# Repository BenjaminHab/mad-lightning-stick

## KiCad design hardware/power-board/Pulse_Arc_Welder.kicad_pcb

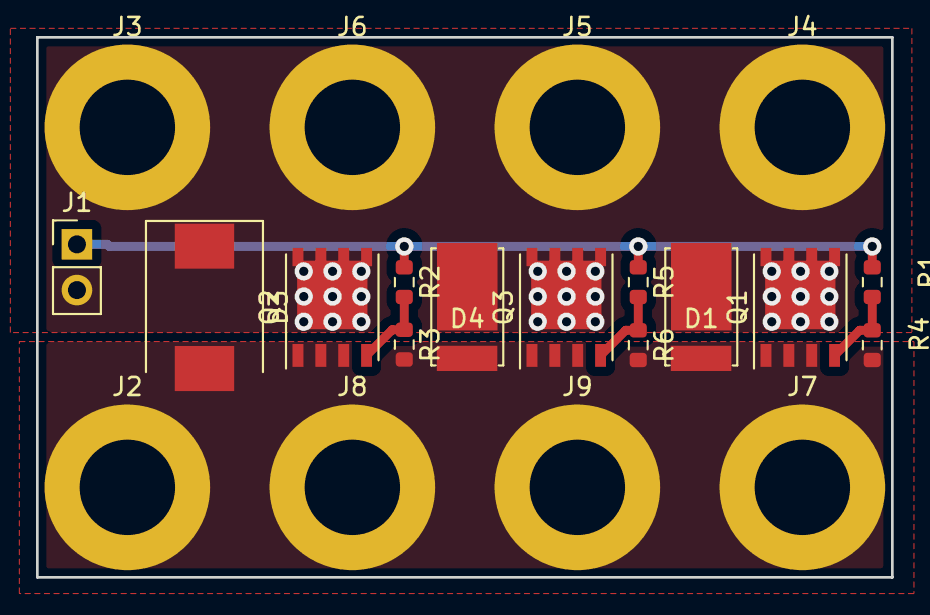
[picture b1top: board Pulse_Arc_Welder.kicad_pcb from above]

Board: 2 copper layers, 47.5 x 30.0 mm, 21 parts (0 on the bottom side), 6 nets.

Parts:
D1, D4: SBR10U45SP5; powerdi5
D3: 24V; D_SMC
J1: to logic board; PinHeader_1x02_P2.54mm_Vertical
J2, J7, J8, J9: BAT-; MountingHole_5.3mm_M5_DIN965_Pad
J3, J4, J5, J6: Electrode; MountingHole_5.3mm_M5_DIN965_Pad
Q1, Q2, Q3: SIR500DP-T1-RE3; PowerPAK_SO-8_Single
R1, R2, R5: 10R; R_0603_1608Metric
R3, R4, R6: 10k; R_0603_1608Metric

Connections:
Electrode: D1.1 (K), D3.1 (K), D4.1 (K), J1.2, J3.1, J4.1, J5.1, J6.1, Q1.5 (D), Q2.5 (D), Q3.5 (D)
GND: D1.2 (A), D3.2 (A), D4.2 (A), J2.1, J7.1, J8.1, J9.1, Q1.1 (S), Q1.2 (S), Q1.3 (S), Q2.1 (S), Q2.2 (S), Q2.3 (S), Q3.1 (S), Q3.2 (S), Q3.3 (S), R3.2, R4.2, R6.2
unnamed: Q2.4 (G), R2.2, R3.1
unnamed: Q3.4 (G), R5.2, R6.1
unnamed: Q1.4 (G), R1.2, R4.1
SIG: J1.1, R1.1, R2.1, R5.1

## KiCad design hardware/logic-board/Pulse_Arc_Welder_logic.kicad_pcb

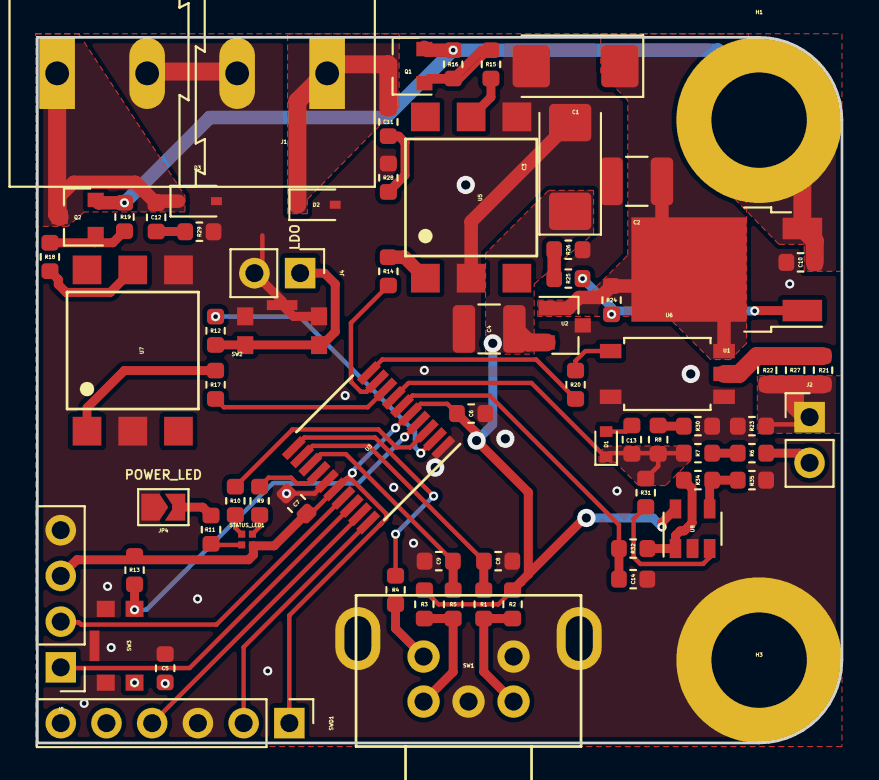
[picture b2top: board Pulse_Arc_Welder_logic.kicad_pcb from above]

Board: 2 copper layers, 44.7 x 39.2 mm, 73 parts (0 on the bottom side), 50 nets.

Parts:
C1, C3: 10uF; CP_EIA-6032-28_Kemet-C
C2, C4: 10uF; C_1210_3225Metric
C5, C6, C7: 1uF; C_0603_1608Metric
C8, C9: 10nF; C_0603_1608Metric
C10: 10uF; C_0603_1608Metric
C11, C12: 220nF; C_0603_1608Metric
C13, C14: 100pF; C_0603_1608Metric
D1: ESD5Z3.3T5G; D_SOD-523
D2, D3: D; D_SOD-323
H1, H3: MountingHole_Pad; MountingHole_5.3mm_M5_DIN965_Pad
J1, J3: Screw_Terminal_01x02; TerminalBlock_Altech_AK300-2_P5.00mm
J2: Conn_01x02_Male; PinHeader_1x02_P2.54mm_Vertical
J4: ARM_SWITCH; PinHeader_1x02_P2.54mm_Vertical
J5: Conn_01x04_Male; PinHeader_1x04_P2.54mm_Vertical
JP4: SolderJumper_2_Open; SolderJumper-2_P1.3mm_Open_TrianglePad1.0x1.5mm
Q1, Q2: Q_PMOS_GSD; SOT-23
R1, R2, R3, R4, R5: 10K; R_0603_1608Metric
R6, R7, R25, R31, R32: 3.3K; R_0603_1608Metric
R8, R14, R17, R20: 330R; R_0603_1608Metric
R9, R10, R11, R15, R18, R24: 1K; R_0603_1608Metric
R12, R13, R16, R19: 10k; R_0603_1608Metric
R21, R22, R27: 10R; R_0603_1608Metric
R23: 4K7; R_0603_1608Metric
R26: 4.7K; R_0603_1608Metric
R28, R29: 100R; R_0603_1608Metric
R30, R35: 470R; R_0603_1608Metric
R34: 33K; R_0603_1608Metric
STATUS_LED1: LED_BGRA
SW1: PEC12R-2225F-S0024; ENCODER_BOURNS
SW2: ARM_BUTTON; KMR7_SWITCH
SW3: RESET; KMR7_SWITCH
SWD1: Conn_01x06_Male; PinHeader_1x06_P2.54mm_Vertical
U1: LD1086BDTTR; TO-252-2
U2: AP7381; SOT-23
U3: STM32F030F4Px; TSSOP-20_4.4x6.5mm_P0.65mm
U5, U7: CNY17-4; PDIP-6
U6: TLP152; SO-6_5PIN
U8: MCP6001-OT; SOT-23-5

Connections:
+3V3: C3.1, C4.1, C6.1, C7.1, J5.3, R2.1, R3.1, R13.1, STATUS_LED1.4, SWD1.1, U2.2, U3.5, U3.16, U8.5
+10V: C1.1, C2.1, R24.1, U1.2, U2.1, U6.6
+24V: C10.1, H1.1, Q1.2, Q2.2, R16.1, R19.1, U1.3
/sheet5D1B3BB1/OUT_HV: C11.1, D2.1, J1.1, Q1.3
/sheet5D1BFFAD/OUT_HV: C12.1, D3.1, J3.1, Q2.3
ARM: J4.1, R12.2, SW2.2
ELECTRODE: J2.2, R6.2
ENCODER_A: C9.1, R5.1, U3.13
ENCODER_B: C8.1, R1.2, U3.12
ENCODER_BUTTON: R4.2, U3.11
GND: C1.2, C2.2, C3.2, C4.2, C5.2, C6.2, C7.2, C8.2, C9.2, C10.2, C14.2, D2.2, D3.2, H3.1, J1.2, J3.2, J4.2, J5.4, JP4.1, R23.2, R26.2, R28.1, R29.1, R30.2, R35.2, SW1.C, SW1.S2, SW1.Shield, SW2.1, SW3.1, SWD1.3, U2.3, U3.1, U3.15, U5.2, U5.4, U6.3, U6.4, U7.2, U7.4, U8.2
I2C_SCL: J5.2, U3.17
I2C_SDA: J5.1, U3.18
LED_GREEN: R10.2, U3.3
LED_RED: R9.2, U3.14
NRST: C5.1, R13.2, SW3.2, SWD1.5, U3.4
unnamed: C11.2, R28.2
unnamed: C12.2, R29.2
unnamed: C13.2, D1.2
unnamed: JP4.2, R11.2
unnamed: Q1.1, R15.1, R16.2
unnamed: Q2.1, R18.1, R19.2
unnamed: R1.1, R2.2, SW1.B
unnamed: R3.2, R5.2, SW1.A
unnamed: R4.1, SW1.S1
unnamed: R6.1, R7.2
unnamed: R9.1, STATUS_LED1.3
unnamed: R10.1, STATUS_LED1.2
unnamed: R11.1, STATUS_LED1.1
unnamed: R12.1, U3.2
unnamed: R14.1, U5.1
unnamed: R15.2, U5.5
unnamed: R17.1, U7.1
unnamed: R18.2, U7.5
unnamed: R20.1, U6.1
unnamed: R21.2, R22.2, R27.2, U6.5
unnamed: R24.2, R25.1, U1.1
unnamed: R25.2, R26.1
unnamed: R8.1, R30.1
unnamed: R31.2, U8.3
unnamed: R32.1, R34.1, U8.1
unnamed: R34.2, R35.1, U8.4
SOLENOID_1: R14.2, U3.9
SOLENOID_2: R17.2, U3.8
SWCLK: SWD1.2, U3.20
SWDIO: SWD1.4, U3.19
TEST_CURRENT: C13.1, D1.1, R7.1, R8.2, R31.1, U3.7
WELD_CURRENT: C14.1, R32.2, U3.6
WELD_HV: J2.1, R21.1, R22.1, R23.1, R27.1
WELD_LV: R20.2, U3.10

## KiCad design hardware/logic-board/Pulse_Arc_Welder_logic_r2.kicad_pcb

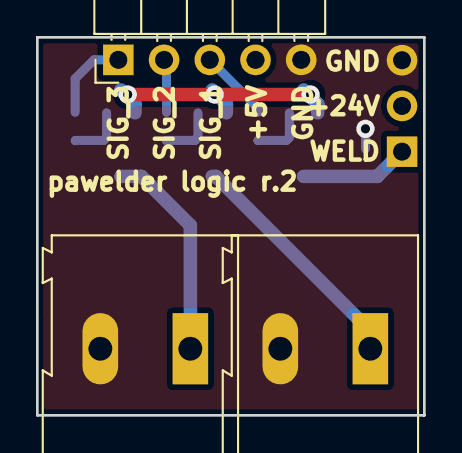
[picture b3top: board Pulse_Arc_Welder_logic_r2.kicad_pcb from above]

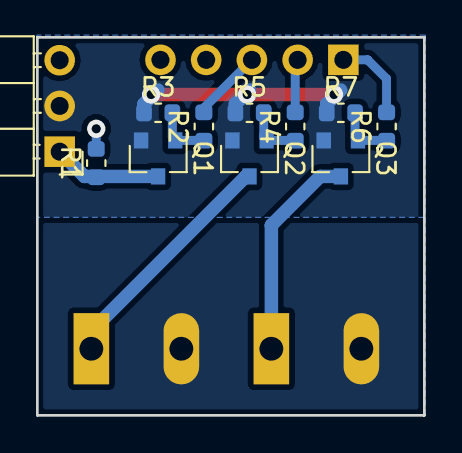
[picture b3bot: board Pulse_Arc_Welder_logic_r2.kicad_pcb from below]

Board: 2 copper layers, 21.5 x 21.0 mm, 14 parts (11 on the bottom side), 11 nets.

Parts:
J1, J4: Screw_Terminal_01x02; TerminalBlock_Altech_AK300-2_P5.00mm
J2: Conn_01x03_Male; PinHeader_1x03_P2.54mm_Horizontal
J3: Conn_01x05_Male; PinHeader_1x05_P2.54mm_Horizontal
Q1, Q2, Q3: Q_PMOS_GSD; SOT-23
R1, R3, R5, R7: 10k; R_0603_1608Metric
R2, R4, R6: 100; R_0603_1608Metric

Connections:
+24V: J2.2, Q1.2, Q2.2, Q3.2, R3.1, R5.1, R7.1
GND: J1.2, J2.3, J3.5, J4.2, R1.2
unnamed: J1.1, Q3.3
unnamed: J4.1, Q2.3
unnamed: Q1.1, R2.1, R3.2
unnamed: Q2.1, R4.1, R5.2
unnamed: Q3.1, R6.1, R7.2
SIG_1: J3.3, R2.2
SIG_2: J3.2, R4.2
SIG_3: J3.1, R6.2
WELD: J2.1, Q1.3, R1.1

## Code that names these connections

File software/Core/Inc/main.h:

/* USER CODE BEGIN Header */
/**
  ******************************************************************************
  * @file           : main.h
  * @brief          : Header for main.c file.
  *                   This file contains the common defines of the application.
  ******************************************************************************
  ** This notice applies to any and all portions of this file
  * that are not between comment pairs USER CODE BEGIN and
  * USER CODE END. Other portions of this file, whether 
  * inserted by the user or by software development tools
  * are owned by their respective copyright owners.
  *
  * COPYRIGHT(c) 2019 STMicroelectronics
  *
  * Redistribution and use in source and binary forms, with or without modification,
  * are permitted provided that the following conditions are met:
  *   1. Redistributions of source code must retain the above copyright notice,
  *      this list of conditions and the following disclaimer.
  *   2. Redistributions in binary form must reproduce the above copyright notice,
  *      this list of conditions and the following disclaimer in the documentation
  *      and/or other materials provided with the distribution.
  *   3. Neither the name of STMicroelectronics nor the names of its contributors
  *      may be used to endorse or promote products derived from this software
  *      without specific prior written permission.
  *
  * THIS SOFTWARE IS PROVIDED BY THE COPYRIGHT HOLDERS AND CONTRIBUTORS "AS IS"
  * AND ANY EXPRESS OR IMPLIED WARRANTIES, INCLUDING, BUT NOT LIMITED TO, THE
  * IMPLIED WARRANTIES OF MERCHANTABILITY AND FITNESS FOR A PARTICULAR PURPOSE ARE
  * DISCLAIMED. IN NO EVENT SHALL THE COPYRIGHT HOLDER OR CONTRIBUTORS BE LIABLE
  * FOR ANY DIRECT, INDIRECT, INCIDENTAL, SPECIAL, EXEMPLARY, OR CONSEQUENTIAL
  * DAMAGES (INCLUDING, BUT NOT LIMITED TO, PROCUREMENT OF SUBSTITUTE GOODS OR
  * SERVICES; LOSS OF USE, DATA, OR PROFITS; OR BUSINESS INTERRUPTION) HOWEVER
  * CAUSED AND ON ANY THEORY OF LIABILITY, WHETHER IN CONTRACT, STRICT LIABILITY,
  * OR TORT (INCLUDING NEGLIGENCE OR OTHERWISE) ARISING IN ANY WAY OUT OF THE USE
  * OF THIS SOFTWARE, EVEN IF ADVISED OF THE POSSIBILITY OF SUCH DAMAGE.
  *
  ******************************************************************************
  */
/* USER CODE END Header */

/* Define to prevent recursive inclusion -------------------------------------*/
#ifndef __MAIN_H
#define __MAIN_H

#ifdef __cplusplus
extern "C" {
#endif

/* Includes ------------------------------------------------------------------*/
#include "stm32f0xx_hal.h"

/* Private includes ----------------------------------------------------------*/
/* USER CODE BEGIN Includes */

/* USER CODE END Includes */

/* Exported types ------------------------------------------------------------*/
/* USER CODE BEGIN ET */


/* USER CODE END ET */

/* Exported constants --------------------------------------------------------*/
/* USER CODE BEGIN EC */

/* USER CODE END EC */

/* Exported macro ------------------------------------------------------------*/
/* USER CODE BEGIN EM */

/* USER CODE END EM */

/* Exported functions prototypes ---------------------------------------------*/
void Error_Handler(void);

/* USER CODE BEGIN EFP */

/* USER CODE END EFP */

/* Private defines -----------------------------------------------------------*/
#define ARM_Pin GPIO_PIN_0
#define ARM_GPIO_Port GPIOF
#define TEST_CURRENT_Pin GPIO_PIN_0
#define TEST_CURRENT_GPIO_Port GPIOA
#define WELD_CURRENT_Pin GPIO_PIN_1
#define WELD_CURRENT_GPIO_Port GPIOA
#define SOLENOID_1_Pin GPIO_PIN_2
#define SOLENOID_1_GPIO_Port GPIOA
#define SOLENOID_2_Pin GPIO_PIN_3
#define SOLENOID_2_GPIO_Port GPIOA
#define WELD_SIGNAL_Pin GPIO_PIN_4
#define WELD_SIGNAL_GPIO_Port GPIOA
#define ENCODER_BUTTON_Pin GPIO_PIN_5
#define ENCODER_BUTTON_GPIO_Port GPIOA
#define ENCODER_A_Pin GPIO_PIN_6
#define ENCODER_A_GPIO_Port GPIOA
#define ENCODER_B_Pin GPIO_PIN_7
#define ENCODER_B_GPIO_Port GPIOA
#define LED_Pin GPIO_PIN_1
#define LED_GPIO_Port GPIOB
/* USER CODE BEGIN Private defines */

#define DEBUG_3V3 1U
//IMPROVE: Add Timer module to setup timers
//IMPROVE: Measure Current and Voltage during pulse
/* USER CODE END Private defines */

#ifdef __cplusplus
}
#endif

#endif /* __MAIN_H */

/************************ (C) COPYRIGHT STMicroelectronics *****END OF FILE****/

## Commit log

2020-11-04 fixed minor statemachine problem
2020-11-04 statemachine progress
2020-11-05 Fixed statemachine initialization error
2020-11-06 Improved ADC Test
2020-11-06 fixed arm button reading in statemachine
2020-11-06 cleanup
2020-11-06 cleanup and added .gitignore
2022-05-19 Begun work on power board r.3
